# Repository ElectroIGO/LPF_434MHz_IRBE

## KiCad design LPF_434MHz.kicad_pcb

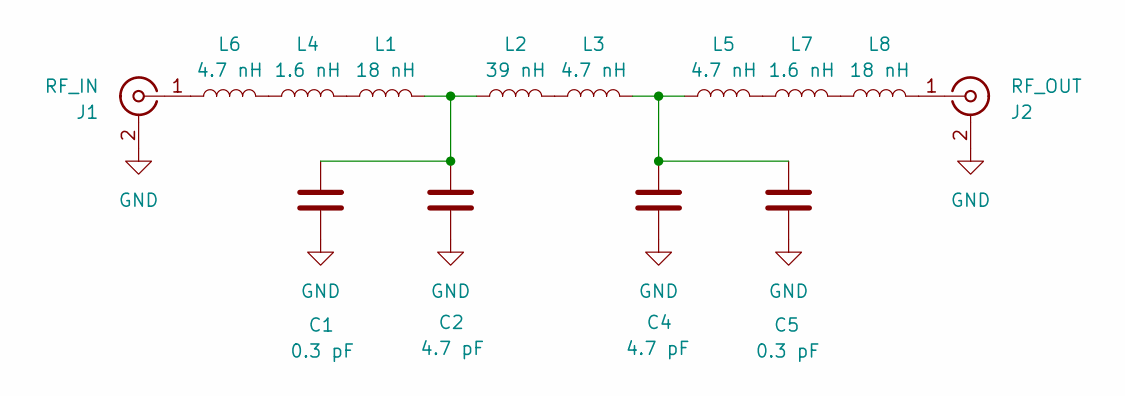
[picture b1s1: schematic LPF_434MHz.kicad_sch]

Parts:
C1, C5: 0.3 pF; C_0603_1608Metric
C2, C4: 4.7 pF; C_0603_1608Metric
J1: RF_IN; SMA_CHINA
J2: RF_OUT; SMA_CHINA
L1, L8: 18 nH; L_0603_1608Metric
L2: 39 nH; L_0603_1608Metric
L3, L5, L6: 4.7 nH; L_0603_1608Metric
L4, L7: 1.6 nH; L_0603_1608Metric

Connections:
GND: C1.2, C2.2, C4.2, C5.2, J1.2 (Ext), J2.2 (Ext)
unnamed: C1.1, C2.1, L1.2, L2.1
unnamed: C4.1, C5.1, L3.2, L5.1
unnamed: J1.1 (In), L6.1
unnamed: J2.1 (In), L8.2
unnamed: L1.1, L4.2
unnamed: L2.2, L3.1
unnamed: L4.1, L6.2
unnamed: L5.2, L7.1
unnamed: L7.2, L8.1

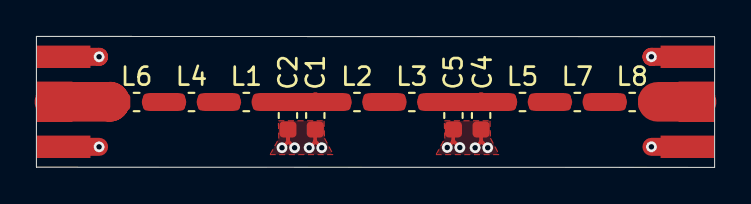
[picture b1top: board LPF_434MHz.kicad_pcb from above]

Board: 2 copper layers, 37.7 x 7.3 mm, 14 parts (0 on the bottom side), 10 nets.

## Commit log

2024-09-11 Finished LPF filter for IRBE 2-way communications
